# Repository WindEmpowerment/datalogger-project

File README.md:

[Development branch!]

This work is HIGHTLY inspired by the openenergymonitor project.

All the work on this repo is under GNU GPL3 licence.

# datalogger-project (EN)
Datalogger's development in order to monitor a wind turbine (wind speed, wind direction, power).

This work is an initiative by Gilles LONGUET from Tripalium and the Measurment working group from WindEmpowerment.

# Organisation :
This datalogger is design on two principal boards, one for the sensor signal adaptation on a second for the numerical work.
Plug the first on the second and you have the hardware to monitor a wind turbine with these possibilities :
- 2 anemometers
- 1 windvane
- 1 AC voltage sensor
- 1 DC voltage sensor
- 4 DC/AC current sensors
- 1 RPM sensors
- 1 temperature sensor
	
The data is available on an UART permanently and with the UART to USB converter you can collect them directly on a computer.
Data can be write on the SD card too.
To transmit the data, you need to chose a transmitter. You can connect a ESP wifi module to send it on your local network or use a GPRS module to transmit on a remote network.
Emoncms is used to collect data on a remote server, to add process on and record data. It's also used to visualize data.

# datalogger-project (FR)
Développement d'un enregistreur de données pour monitorer une éolienne (vitesse et direction du vent et puissance produite).

Ce travail est une initiative de Gilles Longuet pour Tripalium et le Measurment working group de WindEmpowerment.

# Organisation :
Cet enregistreur de données est développé autour de deux cartes, une première pour le traitement des signaux provenant des capteurs et une seconde pour tout le traitement numérique des données.
Il suffit de connecter la première carte sur la seconde pour avoir un enregistreur de données avec les possibilités suivantes :
- 2 anémomètres
- 1 girouette
- 1 sonde de tension AC
- 1 sonde de tension DC
- 4 sondes de courant AC ou DC
- 1 sonde RPM
- 1 sonde de température
	
Les données sont disponibles sur un UART de façon permanente et avec l'adaptateur UART/USB vous pouvez directement collecter les données sur un ordinateur. Les données peuvent aussi être enregistré sur une carte SD.
Pour transmettre les données, vous devez choisir un module. Soit vous utilisez un module du type ESP wifi, pour envoyer vos données sur votre wifi local. Soit vous utilisez un module GPRS pour transmettre les donnés à distances.
Emoncms est utilisé pour la collecte des données sur un serveur distant. On peut appliquer sur les données des processus puis les enregistrer. Emoncms permet aussi la visualisation des données.

# Repositories description :
## Emoncms_add-ons repo :
Contain different add-ons to simplify the wind visualization.

## Firmware :
Contain the software for the microcontroller.

## Hardware :
Contain the files on the different hardware boards.

## windlogger_shield(old) repo :
Contain the work than was done by Etienne, a student. He does that to help us for an internship of 6 weeks. This is an archive, the new version is in the Hardware repo.
The report is in French.

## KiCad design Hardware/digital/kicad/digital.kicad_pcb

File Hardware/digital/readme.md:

# DIGITALs
This board contains all the needs to use an Atmega1284p like an Arduino. But because it's a prototype board, the power is a small shield to be upgradable. On this digital board, the shield can be plug.
A sd card module and a transmitter module can be add too. This permit to collect data on the SD card and/or send it by wifi or gprs.

## BLOCK DIAGRAM

todo

## RENDER PREVIEW

## Todo list
- test
- documentation...

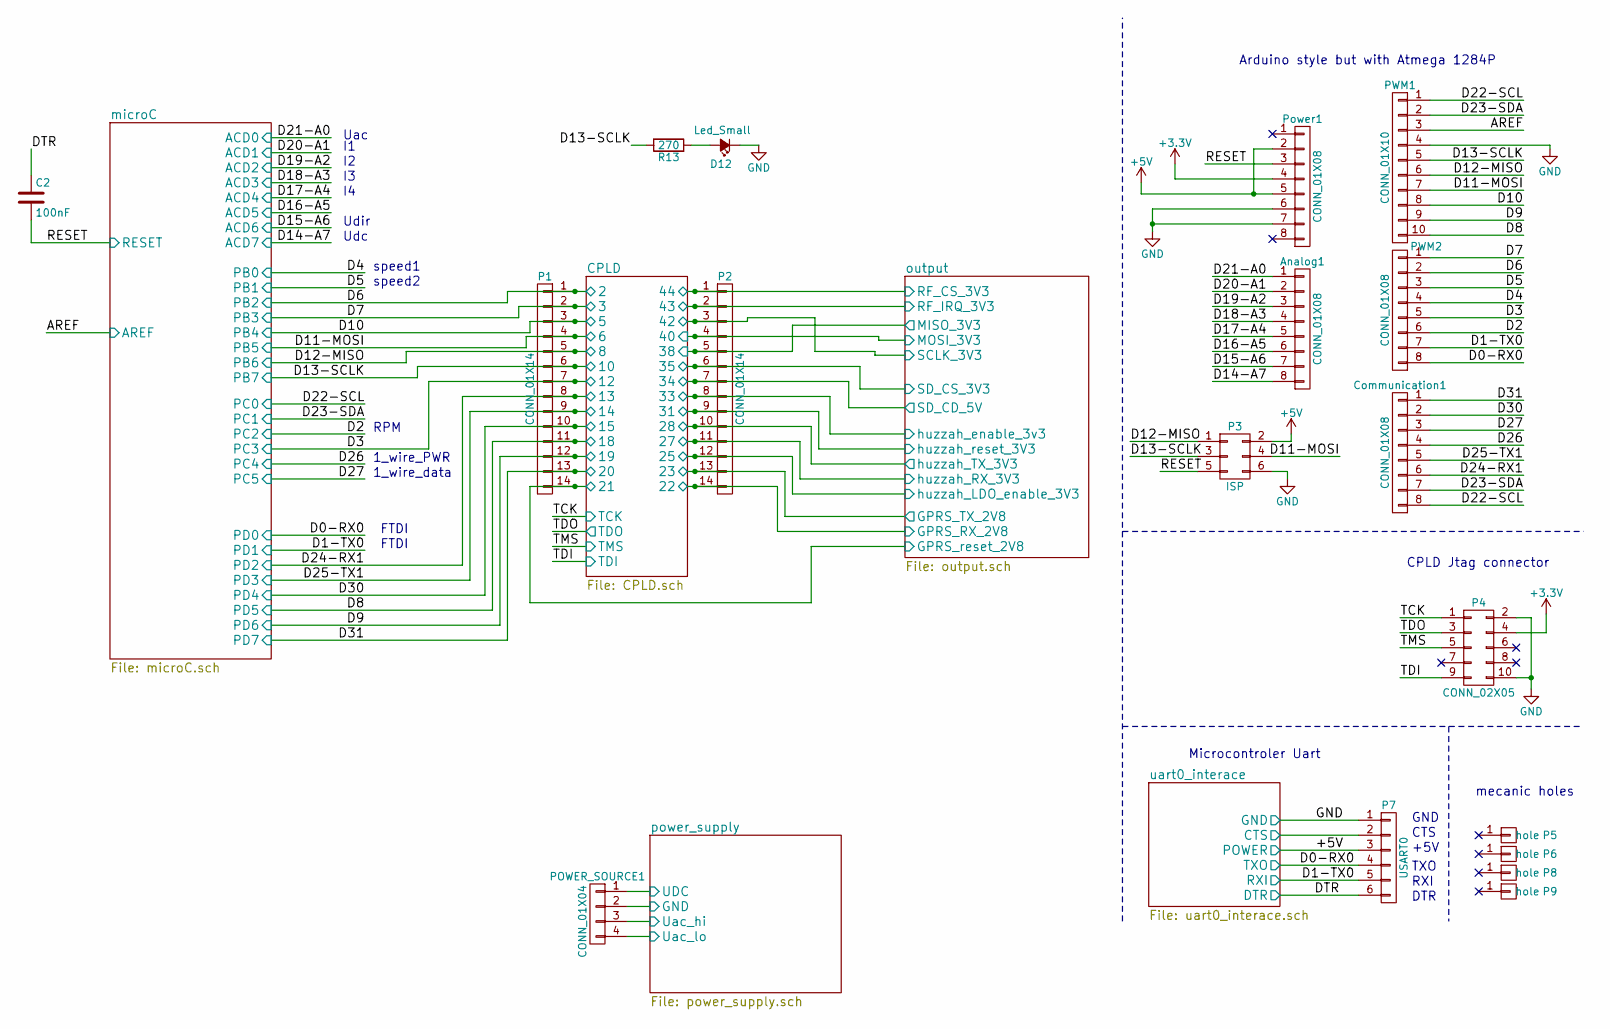
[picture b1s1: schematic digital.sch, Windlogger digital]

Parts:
Analog1: CONN_01X08; Socket_Strip_Straight_1x08
C2: 100nF; C_Rect_L7_W2.5_P5
Communication1: CONN_01X08; Socket_Strip_Straight_1x08
D12: Led_Small; LED-3MM
P1, P2: CONN_01X14; Socket_Strip_Straight_1x14
P3: ISP; Socket_Strip_Straight_2x03
P4: CONN_02X05; Pin_Header_Straight_2x05
P5, P6, P8, P9: hole; Arduino_1pin
P7: USART0; Pin_Header_Straight_1x06
POWER_SOURCE1: CONN_01X04; Socket_Strip_Straight_1x04
PWM1: CONN_01X10; Socket_Strip_Straight_1x10
PWM2: CONN_01X08; Socket_Strip_Straight_1x08
Power1: CONN_01X08; Socket_Strip_Straight_1x08
R13: 270; R3-LARGE_PADS

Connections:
+3V3: P4.4, Power1.4; also elsewhere on the board
+5V: P3.2, P7.3, Power1.2, Power1.5; also elsewhere on the board
/CPLD/2: P1.1, PWM2.2; also elsewhere on the board
/CPLD/3: P1.2, PWM2.1; also elsewhere on the board
/CPLD/5: P1.3, PWM1.8; also elsewhere on the board
/CPLD/6: P1.4, P3.4, PWM1.7; also elsewhere on the board
/CPLD/8: P1.5, P3.1, PWM1.6; also elsewhere on the board
/CPLD/10: P1.6, P3.3, PWM1.5, R13.2; also elsewhere on the board
/CPLD/12: P1.7, PWM2.5; also elsewhere on the board
/CPLD/13: Communication1.6, P1.8; also elsewhere on the board
/CPLD/14: Communication1.5, P1.9; also elsewhere on the board
/CPLD/15: Communication1.2, P1.10; also elsewhere on the board
/CPLD/18: P1.11, PWM1.10; also elsewhere on the board
/CPLD/19: P1.12, PWM1.9; also elsewhere on the board
/CPLD/20: Communication1.1, P1.13; also elsewhere on the board
/CPLD/21: P1.14; also elsewhere on the board
/CPLD/22: P2.14; also elsewhere on the board
/CPLD/23: P2.13; also elsewhere on the board
/CPLD/25: P2.12; also elsewhere on the board
/CPLD/27: P2.11; also elsewhere on the board
/CPLD/28: P2.10; also elsewhere on the board
/CPLD/31: P2.9; also elsewhere on the board
/CPLD/33: P2.8; also elsewhere on the board
/CPLD/34: P2.7; also elsewhere on the board
/CPLD/35: P2.6; also elsewhere on the board
/CPLD/38: P2.5; also elsewhere on the board
/CPLD/40: P2.4; also elsewhere on the board
/CPLD/42: P2.3; also elsewhere on the board
/CPLD/43: P2.2; also elsewhere on the board
/CPLD/44: P2.1; also elsewhere on the board
/CPLD/TCK: P4.1; also elsewhere on the board
/CPLD/TDI: P4.9; also elsewhere on the board
/CPLD/TDO: P4.3; also elsewhere on the board
/CPLD/TMS: P4.5; also elsewhere on the board
/microC/ACD0: Analog1.1; also elsewhere on the board
/microC/ACD1: Analog1.2; also elsewhere on the board
/microC/ACD2: Analog1.3; also elsewhere on the board
/microC/ACD3: Analog1.4; also elsewhere on the board
/microC/ACD4: Analog1.5; also elsewhere on the board
/microC/ACD5: Analog1.6; also elsewhere on the board
/microC/ACD6: Analog1.7; also elsewhere on the board
/microC/ACD7: Analog1.8; also elsewhere on the board
/microC/AREF: PWM1.3; also elsewhere on the board
/microC/PB0: PWM2.4; also elsewhere on the board
/microC/PB1: PWM2.3; also elsewhere on the board
/microC/PC0: Communication1.8, PWM1.1; also elsewhere on the board
/microC/PC1: Communication1.7, PWM1.2; also elsewhere on the board
/microC/PC2: PWM2.6; also elsewhere on the board
/microC/PC4: Communication1.4; also elsewhere on the board
/microC/PC5: Communication1.3; also elsewhere on the board
/microC/PD0: P7.4, PWM2.8; also elsewhere on the board
/microC/PD1: P7.5, PWM2.7; also elsewhere on the board
/microC/RESET: C2.2, P3.5, Power1.3; also elsewhere on the board
/power_supply/UDC: POWER_SOURCE1.1; also elsewhere on the board
/power_supply/Uac_hi: POWER_SOURCE1.3; also elsewhere on the board
/power_supply/Uac_lo: POWER_SOURCE1.4; also elsewhere on the board
/uart0_interace/CTS: P7.2; also elsewhere on the board
/uart0_interace/DTR: C2.1, P7.6; also elsewhere on the board
GND: D12.1 (K), P3.6, P4.2, P4.10, P7.1, POWER_SOURCE1.2, PWM1.4, Power1.6, Power1.7; also elsewhere on the board
unnamed: D12.2 (A), R13.1

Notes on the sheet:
mecanic holes
Arduino style but with Atmega 1284P
DTR
RXI
TXO
GND
+5V
CTS
CPLD Jtag connector
Microcontroler Uart
Uac
Udir
Udc
speed1
speed2
1_wire_PWR
1_wire_data
FTDI
RPM

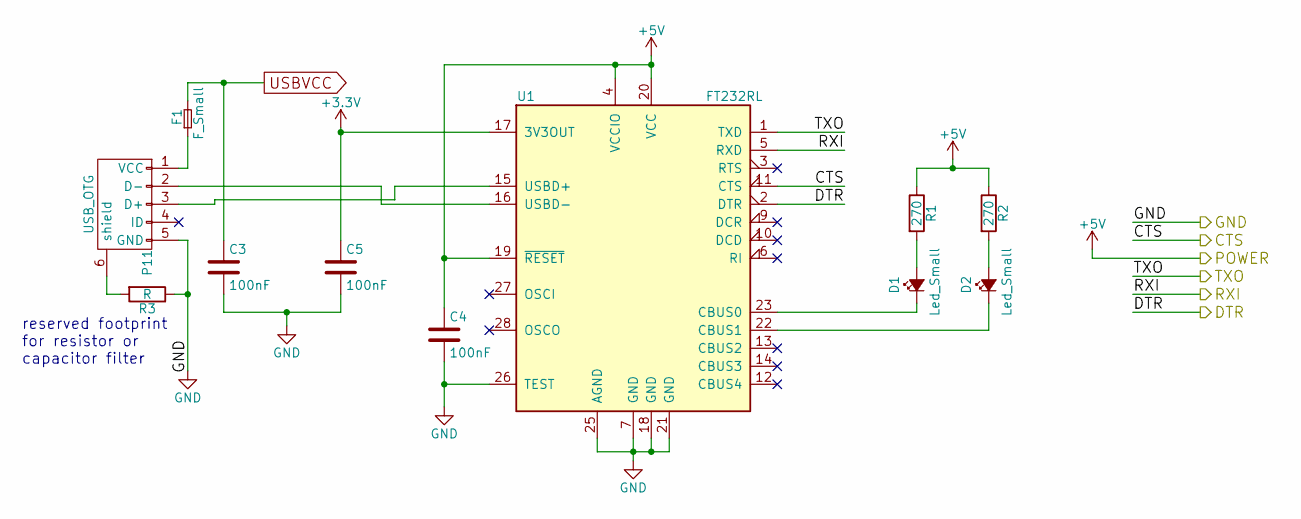
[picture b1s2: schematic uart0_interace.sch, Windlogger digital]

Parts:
C3, C4, C5: 100nF; C_Rect_L7_W2.5_P5
D1, D2: Led_Small; LED-3MM
F1: F_Small; Fuse_TE5_Littlefuse-395Series
P11: USB_OTG; USB_Micro-B_10103594-0001LF
R1, R2: 270; R3-LARGE_PADS
R3: R; R3-LARGE_PADS
U1: FT232RL; SSOP-28_5.3x10.2mm_Pitch0.65mm

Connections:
+3V3: C5.1, U1.17 (3V3OUT); also elsewhere on the board
+5V: C4.1, R1.1, R2.1, U1.4 (VCCIO), U1.19 (~RESET~), U1.20 (VCC); also elsewhere on the board
/microC/PD0: U1.1 (TXD); also elsewhere on the board
/microC/PD1: U1.5 (RXD); also elsewhere on the board
/uart0_interace/CTS: U1.11 (CTS); also elsewhere on the board
/uart0_interace/DTR: U1.2 (DTR); also elsewhere on the board
GND: C3.2, C4.2, C5.2, P11.5 (GND), R3.1, U1.7 (GND), U1.18 (GND), U1.21 (GND), U1.25 (AGND), U1.26 (TEST); also elsewhere on the board
unnamed: D1.1 (K), U1.23 (CBUS0)
unnamed: D1.2 (A), R1.2
unnamed: D2.1 (K), U1.22 (CBUS1)
unnamed: D2.2 (A), R2.2
unnamed: F1.1, P11.1 (VCC)
unnamed: P11.2 (D-), U1.16 (USBD-)
unnamed: P11.3 (D+), U1.15 (USBD+)
unnamed: P11.6 (shield), R3.2
USBVCC: C3.1, F1.2; also elsewhere on the board

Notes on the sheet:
reserved footprint for resistor or capacitor filter

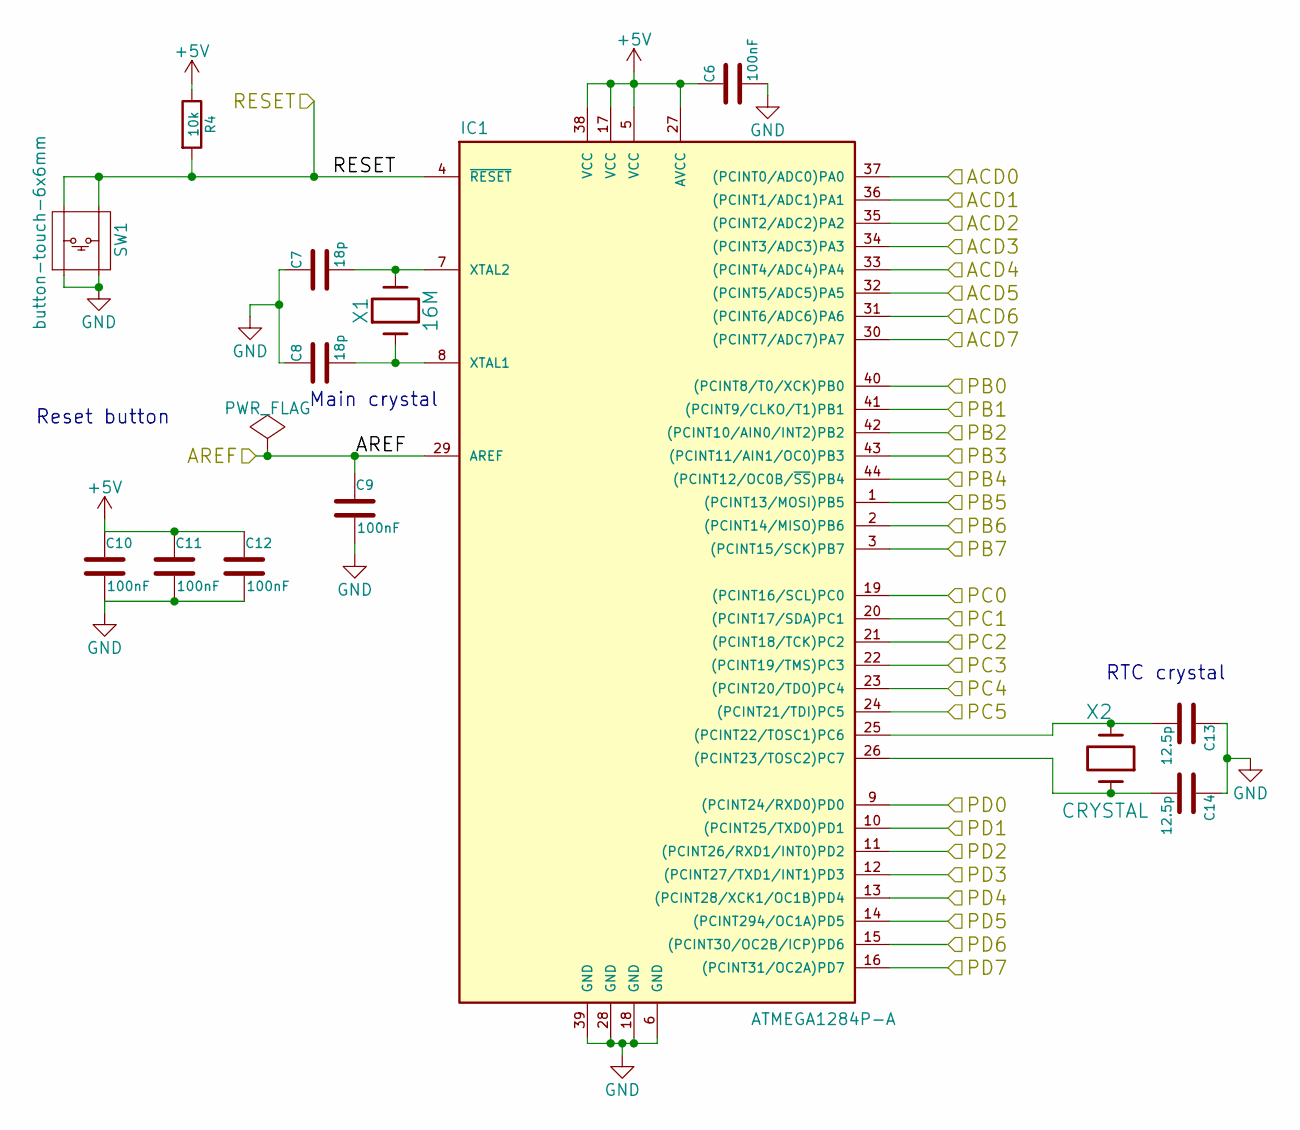
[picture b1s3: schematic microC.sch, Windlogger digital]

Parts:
C6, C9, C10, C11, C12: 100nF; C_Rect_L7_W2.5_P5
C7, C8: 18p; C_Rect_L4_W2.5_P2.5
C13, C14: 12.5p; C_Rect_L4_W2.5_P2.5
IC1: ATMEGA1284P-A; TQFP-44_10x10mm_Pitch0.8mm
R4: 10k; R3-LARGE_PADS
SW1: button-touch-6x6mm
X1: 16M; Crystal_HC49-U_Vertical
X2: CRYSTAL; Crystal_Round_Horizontal_3mm_BigPad

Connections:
+5V: C6.1, C10.1, C11.1, C12.1, IC1.5 (VCC), IC1.17 (VCC), IC1.27 (AVCC), IC1.38 (VCC), R4.1; also elsewhere on the board
/CPLD/2: IC1.42 ((PCINT10/AIN0/INT2)PB2); also elsewhere on the board
/CPLD/3: IC1.43 ((PCINT11/AIN1/OC0)PB3); also elsewhere on the board
/CPLD/5: IC1.44 ((PCINT12/OC0B/~SS~)PB4); also elsewhere on the board
/CPLD/6: IC1.1 ((PCINT13/MOSI)PB5); also elsewhere on the board
/CPLD/8: IC1.2 ((PCINT14/MISO)PB6); also elsewhere on the board
/CPLD/10: IC1.3 ((PCINT15/SCK)PB7); also elsewhere on the board
/CPLD/12: IC1.22 ((PCINT19/TMS)PC3); also elsewhere on the board
/CPLD/13: IC1.11 ((PCINT26/RXD1/INT0)PD2); also elsewhere on the board
/CPLD/14: IC1.12 ((PCINT27/TXD1/INT1)PD3); also elsewhere on the board
/CPLD/15: IC1.13 ((PCINT28/XCK1/OC1B)PD4); also elsewhere on the board
/CPLD/18: IC1.14 ((PCINT294/OC1A)PD5); also elsewhere on the board
/CPLD/19: IC1.15 ((PCINT30/OC2B/ICP)PD6); also elsewhere on the board
/CPLD/20: IC1.16 ((PCINT31/OC2A)PD7); also elsewhere on the board
/microC/ACD0: IC1.37 ((PCINT0/ADC0)PA0); also elsewhere on the board
/microC/ACD1: IC1.36 ((PCINT1/ADC1)PA1); also elsewhere on the board
/microC/ACD2: IC1.35 ((PCINT2/ADC2)PA2); also elsewhere on the board
/microC/ACD3: IC1.34 ((PCINT3/ADC3)PA3); also elsewhere on the board
/microC/ACD4: IC1.33 ((PCINT4/ADC4)PA4); also elsewhere on the board
/microC/ACD5: IC1.32 ((PCINT5/ADC5)PA5); also elsewhere on the board
/microC/ACD6: IC1.31 ((PCINT6/ADC6)PA6); also elsewhere on the board
/microC/ACD7: IC1.30 ((PCINT7/ADC7)PA7); also elsewhere on the board
/microC/AREF: C9.1, IC1.29 (AREF); also elsewhere on the board
/microC/PB0: IC1.40 ((PCINT8/T0/XCK)PB0); also elsewhere on the board
/microC/PB1: IC1.41 ((PCINT9/CLKO/T1)PB1); also elsewhere on the board
/microC/PC0: IC1.19 ((PCINT16/SCL)PC0); also elsewhere on the board
/microC/PC1: IC1.20 ((PCINT17/SDA)PC1); also elsewhere on the board
/microC/PC2: IC1.21 ((PCINT18/TCK)PC2); also elsewhere on the board
/microC/PC4: IC1.23 ((PCINT20/TDO)PC4); also elsewhere on the board
/microC/PC5: IC1.24 ((PCINT21/TDI)PC5); also elsewhere on the board
/microC/PD0: IC1.9 ((PCINT24/RXD0)PD0); also elsewhere on the board
/microC/PD1: IC1.10 ((PCINT25/TXD0)PD1); also elsewhere on the board
/microC/RESET: IC1.4 (~RESET), R4.2, SW1.2, SW1.4; also elsewhere on the board
GND: C6.2, C7.1, C8.1, C9.2, C10.2, C11.2, C12.2, C13.1, C14.1, IC1.6 (GND), IC1.18 (GND), IC1.28 (GND), IC1.39 (GND), SW1.1, SW1.3; also elsewhere on the board
unnamed: C7.2, IC1.7 (XTAL2), X1.2
unnamed: C8.2, IC1.8 (XTAL1), X1.1
unnamed: C13.2, IC1.25 ((PCINT22/TOSC1)PC6), X2.2
unnamed: C14.2, IC1.26 ((PCINT23/TOSC2)PC7), X2.1

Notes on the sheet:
Main crystal
RTC crystal
Reset button

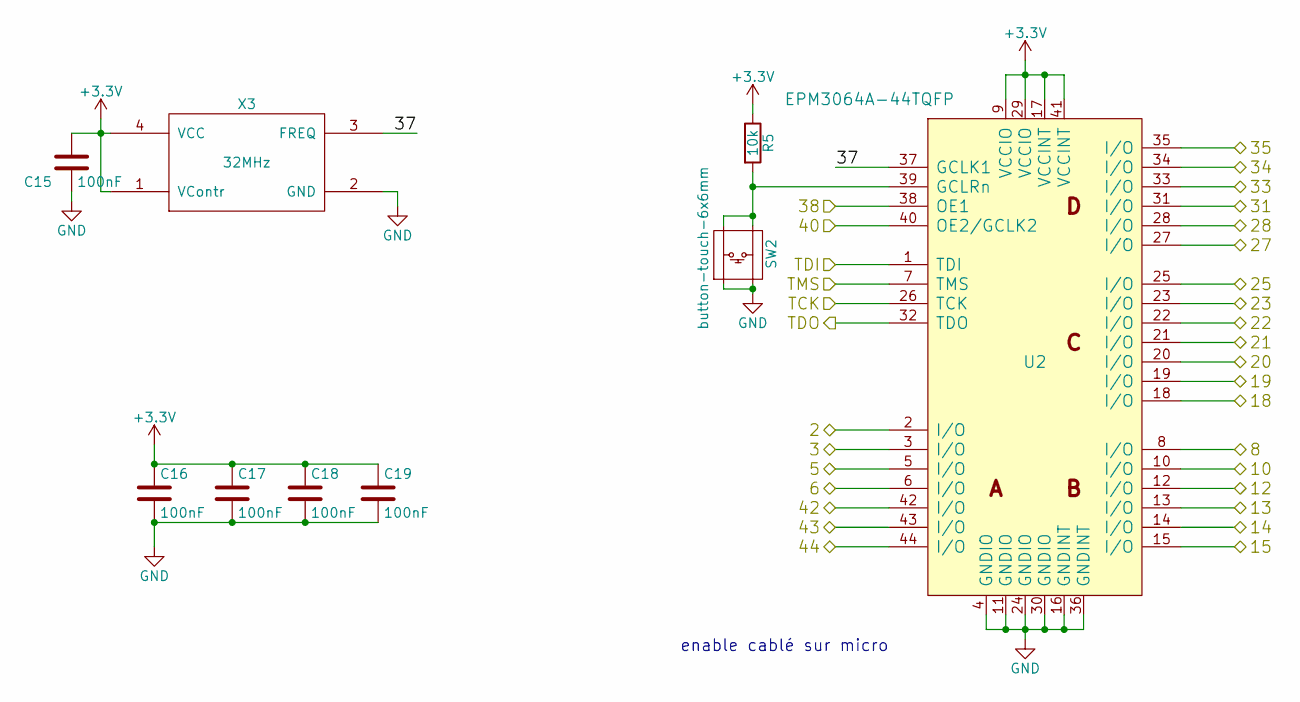
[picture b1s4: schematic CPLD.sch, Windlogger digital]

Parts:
C15, C16, C17, C18, C19: 100nF; C_Rect_L7_W2.5_P5
R5: 10k; R3-LARGE_PADS
SW2: button-touch-6x6mm
U2: EPM3064A-44TQFP; TQFP-44_10x10mm_Pitch0.8mm
X3: 32MHz; oscillator-7x5mm

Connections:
+3V3: C15.1, C16.1, C17.1, C18.1, C19.1, R5.1, U2.9 (VCCIO), U2.17 (VCCINT), U2.29 (VCCIO), U2.41 (VCCINT), X3.1 (VContr), X3.4 (VCC); also elsewhere on the board
/CPLD/2: U2.2 (I/O); also elsewhere on the board
/CPLD/3: U2.3 (I/O); also elsewhere on the board
/CPLD/5: U2.5 (I/O); also elsewhere on the board
/CPLD/6: U2.6 (I/O); also elsewhere on the board
/CPLD/8: U2.8 (I/O); also elsewhere on the board
/CPLD/10: U2.10 (I/O); also elsewhere on the board
/CPLD/12: U2.12 (I/O); also elsewhere on the board
/CPLD/13: U2.13 (I/O); also elsewhere on the board
/CPLD/14: U2.14 (I/O); also elsewhere on the board
/CPLD/15: U2.15 (I/O); also elsewhere on the board
/CPLD/18: U2.18 (I/O); also elsewhere on the board
/CPLD/19: U2.19 (I/O); also elsewhere on the board
/CPLD/20: U2.20 (I/O); also elsewhere on the board
/CPLD/21: U2.21 (I/O); also elsewhere on the board
/CPLD/22: U2.22 (I/O); also elsewhere on the board
/CPLD/23: U2.23 (I/O); also elsewhere on the board
/CPLD/25: U2.25 (I/O); also elsewhere on the board
/CPLD/27: U2.27 (I/O); also elsewhere on the board
/CPLD/28: U2.28 (I/O); also elsewhere on the board
/CPLD/31: U2.31 (I/O); also elsewhere on the board
/CPLD/33: U2.33 (I/O); also elsewhere on the board
/CPLD/34: U2.34 (I/O); also elsewhere on the board
/CPLD/35: U2.35 (I/O); also elsewhere on the board
/CPLD/37: U2.37 (GCLK1), X3.3 (FREQ)
/CPLD/38: U2.38 (OE1); also elsewhere on the board
/CPLD/40: U2.40 (OE2/GCLK2); also elsewhere on the board
/CPLD/42: U2.42 (I/O); also elsewhere on the board
/CPLD/43: U2.43 (I/O); also elsewhere on the board
/CPLD/44: U2.44 (I/O); also elsewhere on the board
/CPLD/TCK: U2.26 (TCK); also elsewhere on the board
/CPLD/TDI: U2.1 (TDI); also elsewhere on the board
/CPLD/TDO: U2.32 (TDO); also elsewhere on the board
/CPLD/TMS: U2.7 (TMS); also elsewhere on the board
GND: C15.2, C16.2, C17.2, C18.2, C19.2, SW2.1, SW2.3, U2.4 (GNDIO), U2.11 (GNDIO), U2.16 (GNDINT), U2.24 (GNDIO), U2.30 (GNDIO), U2.36 (GNDINT), X3.2 (GND); also elsewhere on the board
unnamed: R5.2, SW2.2, SW2.4, U2.39 (GCLRn)

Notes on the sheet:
enable cablé sur micro

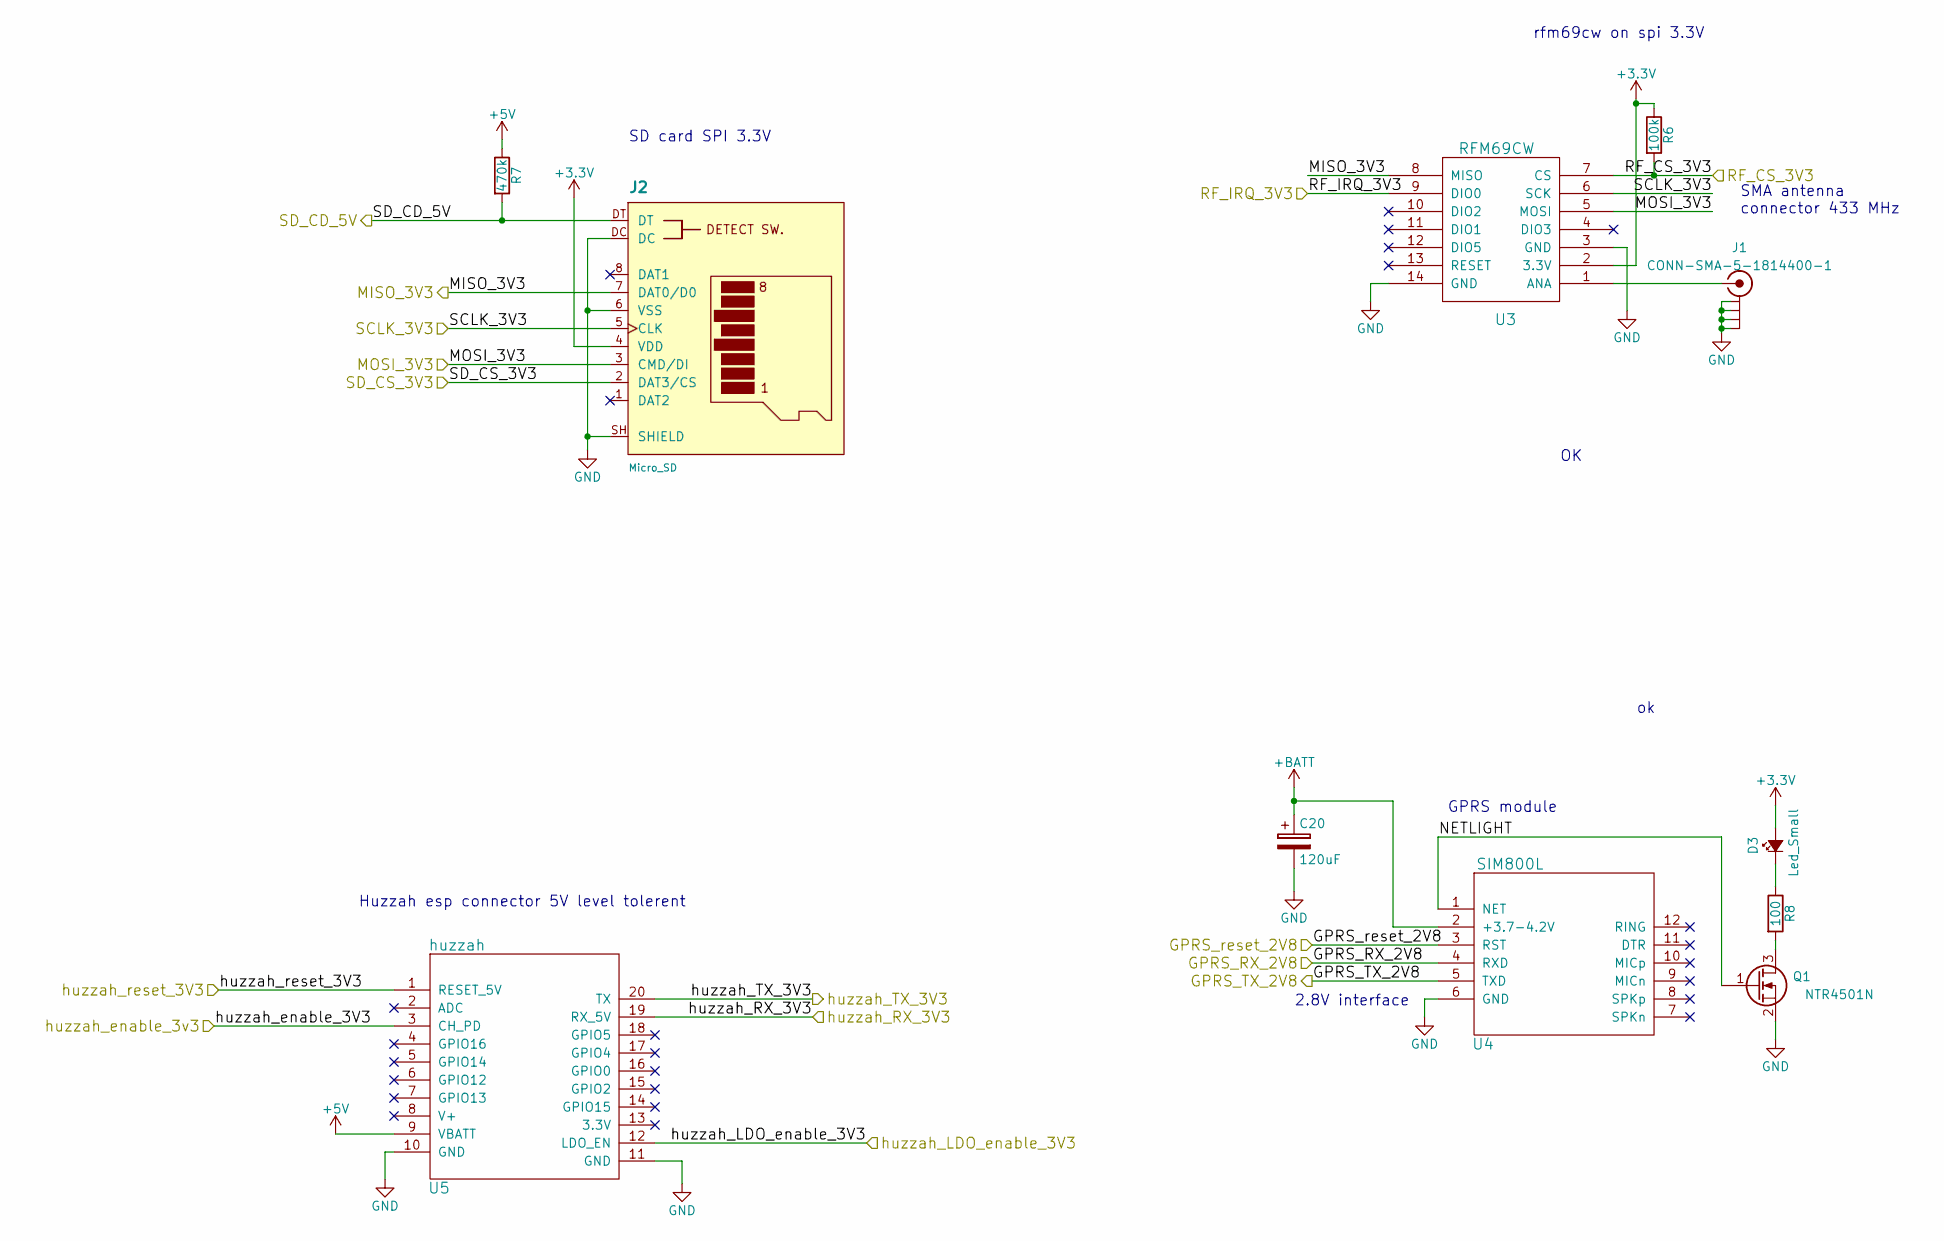
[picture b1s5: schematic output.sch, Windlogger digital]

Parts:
C20: 120uF; C_Radial_D6.3_L11.2_P2.5
D3: Led_Small; LED-3MM
J1: CONN-SMA-5-1814400-1; conn-SMA_TE-5-1814400-1
J2: Micro_SD; HIROSE-MICROSD-DM3AT-SF
Q1: NTR4501N; SOT-23_Handsoldering
R6: 100k; R3-LARGE_PADS
R7: 470k; R3-LARGE_PADS
R8: 100; R3-LARGE_PADS
U3: RFM69CW
U4: SIM800L; GPRS-SIM80L-smaller
U5: huzzah; adafruit-huzzah

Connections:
+3V3: D3.2 (A), J2.4 (VDD), R6.1, U3.2 (3.3V); also elsewhere on the board
+5V: R7.1, U5.9 (VBATT); also elsewhere on the board
+BATT: C20.1, U4.2 (+3.7-4.2V); also elsewhere on the board
/CPLD/21: U4.3 (RST); also elsewhere on the board
/CPLD/22: U4.4 (RXD); also elsewhere on the board
/CPLD/23: U4.5 (TXD); also elsewhere on the board
/CPLD/25: U5.12 (LDO_EN); also elsewhere on the board
/CPLD/27: U5.19 (RX_5V); also elsewhere on the board
/CPLD/28: U5.20 (TX); also elsewhere on the board
/CPLD/31: U5.1 (RESET_5V); also elsewhere on the board
/CPLD/33: U5.3 (CH_PD); also elsewhere on the board
/CPLD/34: J2.DT, R7.2; also elsewhere on the board
/CPLD/35: J2.2 (DAT3/CS); also elsewhere on the board
/CPLD/38: J2.7 (DAT0/D0), U3.8 (MISO); also elsewhere on the board
/CPLD/40: J2.3 (CMD/DI), U3.5 (MOSI); also elsewhere on the board
/CPLD/42: J2.5 (CLK), U3.6 (SCK); also elsewhere on the board
/CPLD/43: U3.9 (DIO0); also elsewhere on the board
/CPLD/44: R6.2, U3.7 (CS); also elsewhere on the board
/output/NETLIGHT: Q1.1 (G), U4.1 (NET)
GND: C20.2, J1.2, J1.3, J1.4, J1.5, J2.6 (VSS), J2.DC, J2.SH (SHIELD), Q1.2 (S), U3.3 (GND), U3.14 (GND), U4.6 (GND), U5.10 (GND), U5.11 (GND); also elsewhere on the board
unnamed: D3.1 (K), R8.1
unnamed: J1.1, U3.1 (ANA)
unnamed: Q1.3 (D), R8.2

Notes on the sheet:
rfm69cw on spi 3.3V
Huzzah esp connector 5V level tolerent
GPRS module
SD card SPI 3.3V
2.8V interface
SMA antenna connector 433 MHz

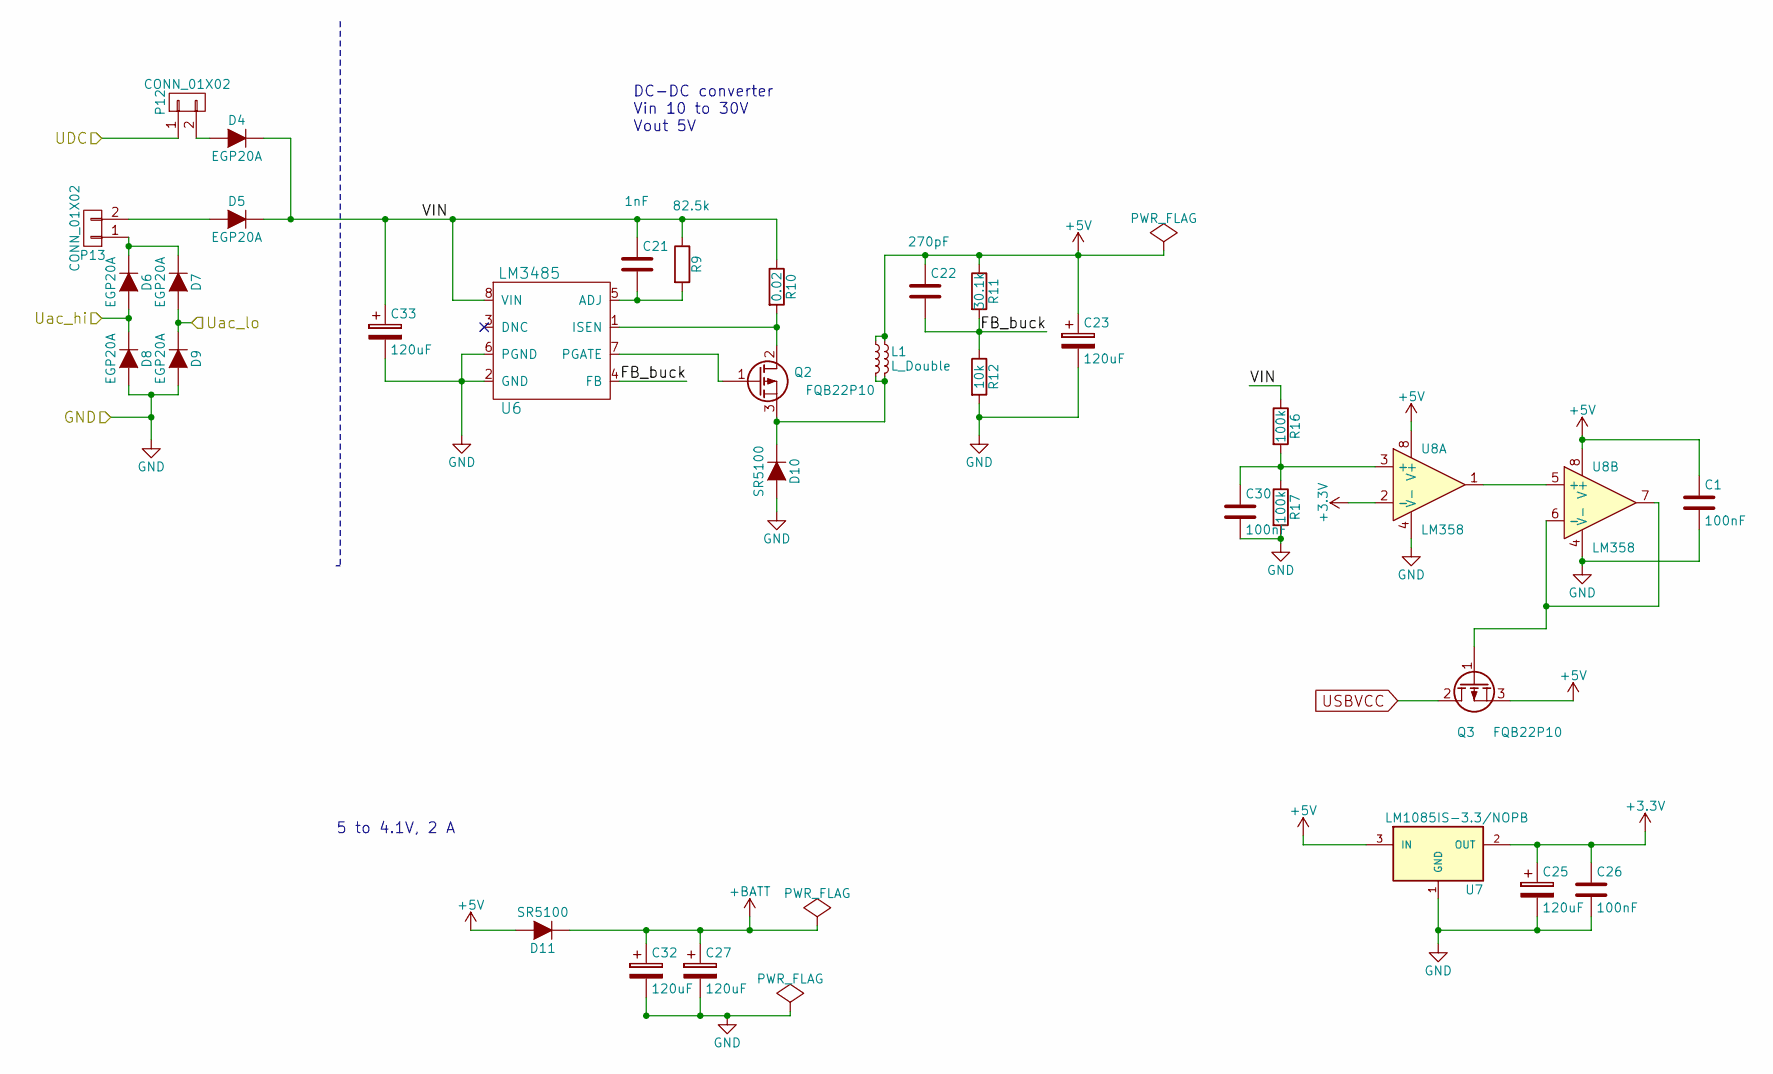
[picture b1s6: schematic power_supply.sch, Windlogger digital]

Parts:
C1, C26, C30: 100nF; C_Rect_L7_W2.5_P5
C21: 1nF; C_Rect_L7_W2.5_P5
C22: 270pF; C_Rect_L4_W2.5_P2.5
C23, C25, C27, C32, C33: 120uF; C_Radial_D6.3_L11.2_P2.5
D4, D5, D6, D7, D8, D9: EGP20A; Diode_DO-35_SOD27_Horizontal_RM10
D10, D11: SR5100; Diode_DO-35_SOD27_Horizontal_RM10
L1: L_Double; DRQ_127
P12, P13: CONN_01X02; Pin_Header_Straight_1x02
Q2, Q3: FQB22P10; D2PAK_2pins
R9: 82.5k; R3-LARGE_PADS
R10: 0.02; R4-LARGE_PADS
R11: 30.1k; R3-LARGE_PADS
R12: 10k; R3-LARGE_PADS
R16, R17: 100k; R3-LARGE_PADS
U6: LM3485; MSOP-8_3x3mm_Pitch0.65mm
U7: LM1085IS-3.3/NOPB; D2PAK_3pins
U8: LM358; DIP-8_W7.62mm_LongPads

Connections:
+3V3: C25.1, C26.1, U7.2 (OUT), U8.2 (-); also elsewhere on the board
+5V: C1.1, C22.1, C23.1, D11.2 (A), L1.1, L1.2, Q3.3 (S), R11.1, U7.3 (IN), U8.8 (V+); also elsewhere on the board
+BATT: C27.1, C32.1, D11.1 (K); also elsewhere on the board
/power_supply/FB_buck: C22.2, R11.2, R12.1, U6.4 (FB)
/power_supply/UDC: P12.1; also elsewhere on the board
/power_supply/Uac_hi: D6.2 (A), D8.1 (K); also elsewhere on the board
/power_supply/Uac_lo: D7.2 (A), D9.1 (K); also elsewhere on the board
/power_supply/VIN: C21.1, C33.1, D4.1 (K), D5.1 (K), R9.1, R10.1, R16.1, U6.8 (VIN)
GND: C1.2, C23.2, C25.2, C26.2, C27.2, C30.2, C32.2, C33.2, D8.2 (A), D9.2 (A), D10.2 (A), R12.2, R17.2, U6.2 (GND), U6.6 (PGND), U7.1 (GND), U8.4 (V-); also elsewhere on the board
unnamed: C21.2, R9.2, U6.5 (ADJ)
unnamed: C30.1, R16.2, R17.1, U8.3 (+)
unnamed: D4.2 (A), P12.2
unnamed: D5.2 (A), P13.2
unnamed: D6.1 (K), D7.1 (K), P13.1
unnamed: D10.1 (K), L1.3, L1.4, Q2.3 (S)
unnamed: Q2.1 (G), U6.7 (PGATE)
unnamed: Q2.2 (D), R10.2, U6.1 (ISEN)
unnamed: Q3.1 (G), U8.6 (-), U8.7
unnamed: U8.1, U8.5 (+)
USBVCC: Q3.2 (D); also elsewhere on the board

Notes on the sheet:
DC-DC converter Vin 10 to 30V Vout 5V
5 to 4.1V, 2 A

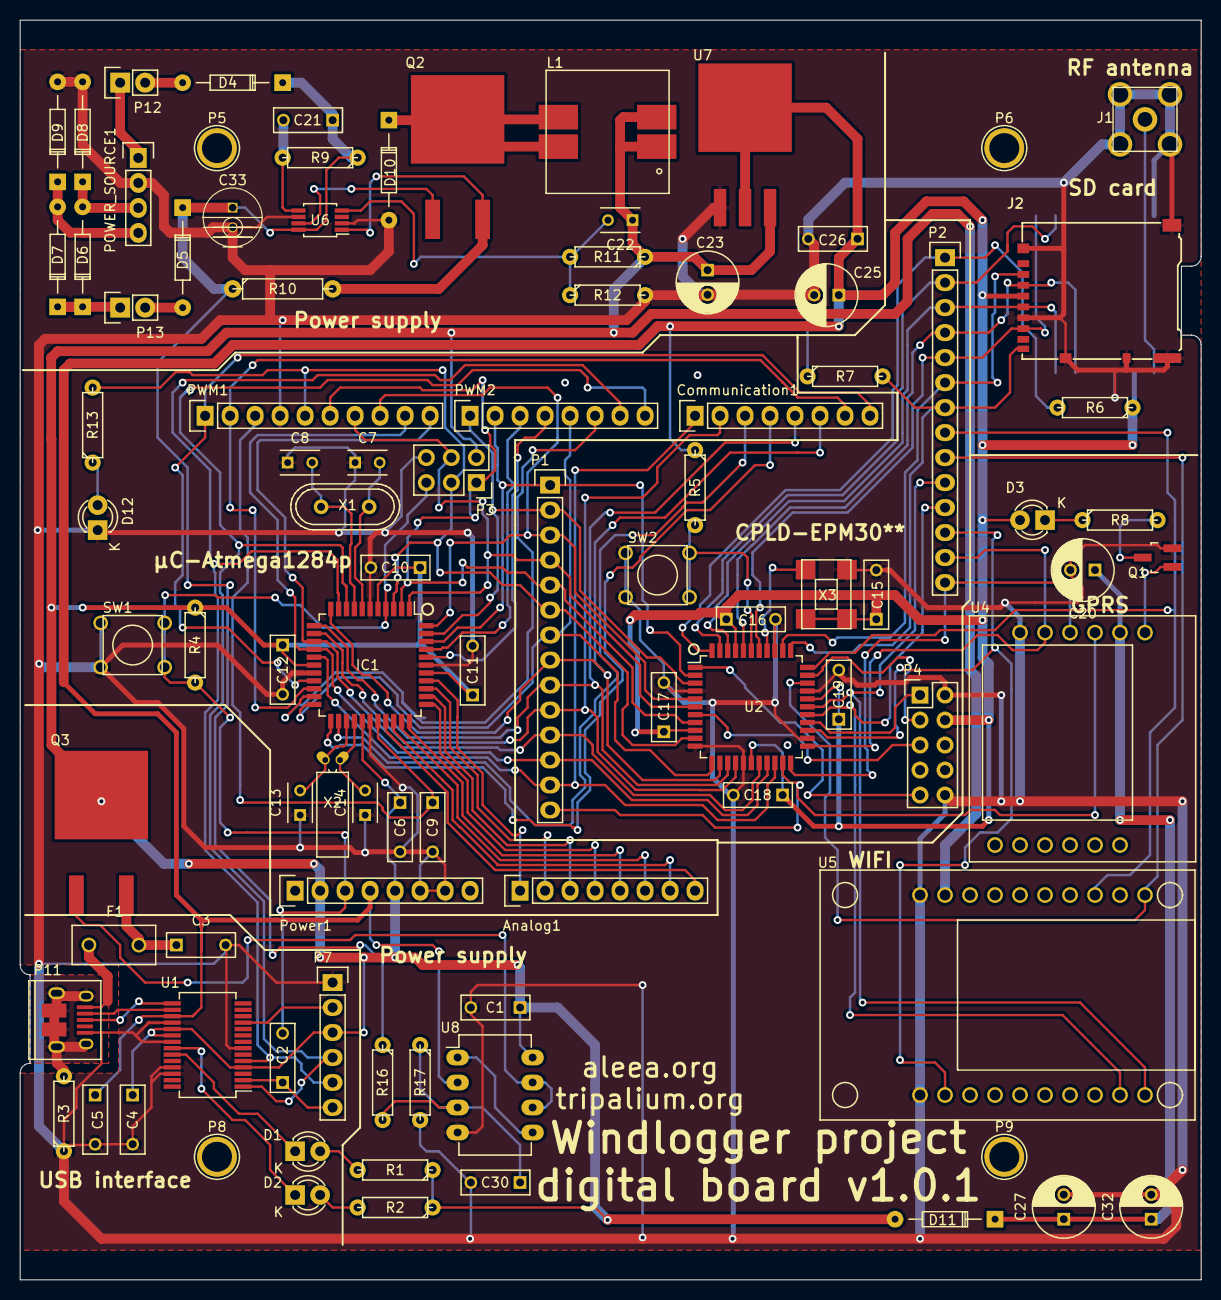
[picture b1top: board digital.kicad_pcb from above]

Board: 2 copper layers, 120.0 x 128.0 mm, 95 parts (1 on the bottom side), 92 nets.

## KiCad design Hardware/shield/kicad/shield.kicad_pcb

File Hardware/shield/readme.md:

# SHIELD
This board contains the functions to convert the signals from sensors to signals for the microcontroller.

This board is design to be plug in the digital board, but you can use it with an arduino uno or mega.

Comment are insert in the schematic, open the kicad project or the pdf export to read those.

## BLOCK DIAGRAM

## RENDER PREVIEW

## Todo list
- chose the componants
- update the BOM
- route the board
- test

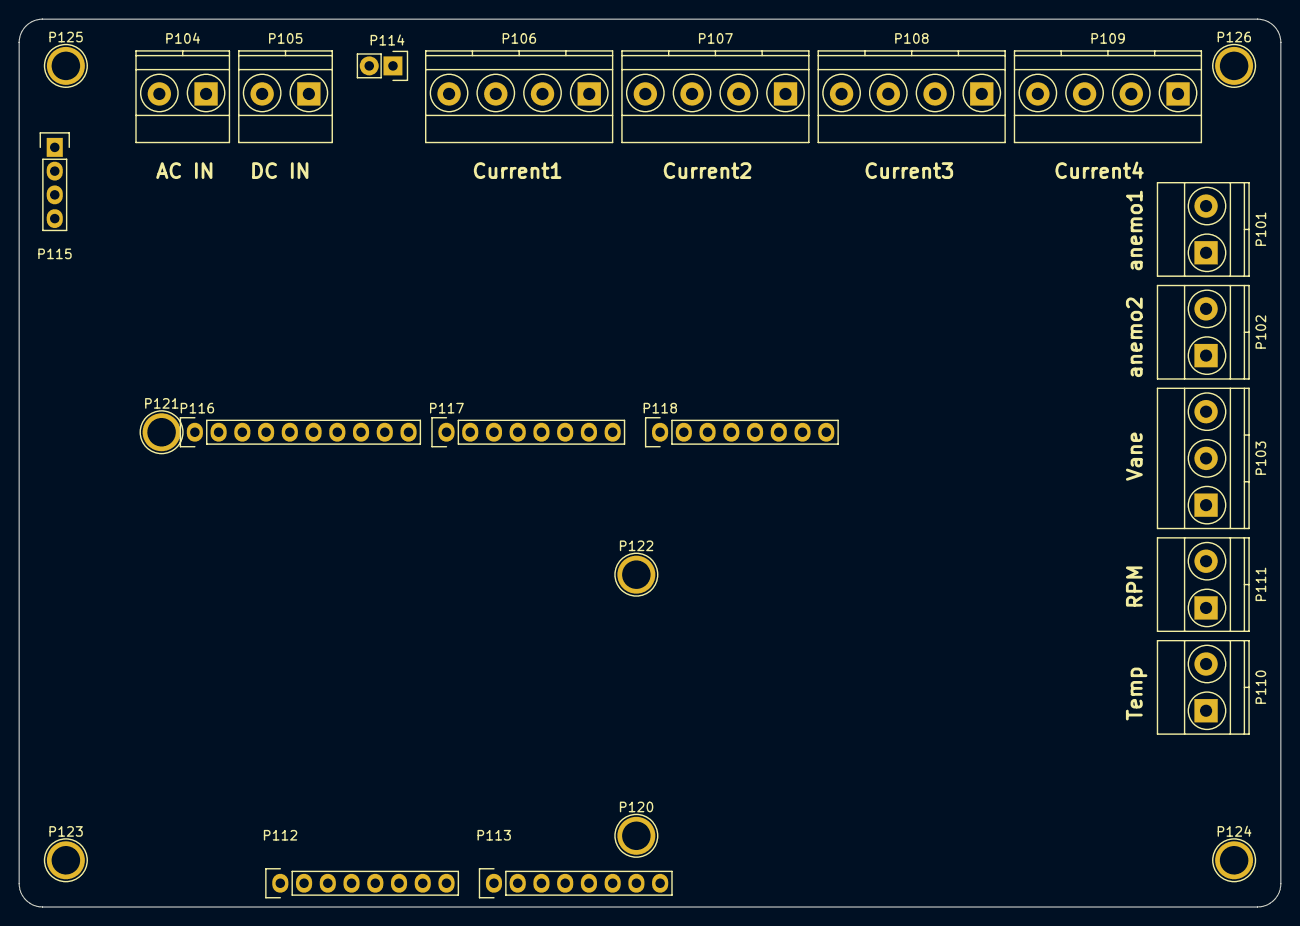
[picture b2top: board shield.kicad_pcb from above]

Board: 2 copper layers, 135.0 x 95.0 mm, 25 parts (0 on the bottom side), 6 nets, no tracks yet.

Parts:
P101: anemo1; TerminalBlock_Pheonix_MKDS1.5-2pol
P102: anemo2; TerminalBlock_Pheonix_MKDS1.5-2pol
P103: vane; TerminalBlock_Pheonix_MKDS1.5-3pol
P104: AC_in; TerminalBlock_Pheonix_MKDS1.5-2pol
P105: DC_in; TerminalBlock_Pheonix_MKDS1.5-2pol
P106: current1; TerminalBlock_Pheonix_MKDS1.5-4pol
P107: current2; TerminalBlock_Pheonix_MKDS1.5-4pol
P108: current3; TerminalBlock_Pheonix_MKDS1.5-4pol
P109: current4; TerminalBlock_Pheonix_MKDS1.5-4pol
P110: temp; TerminalBlock_Pheonix_MKDS1.5-2pol
P111: RPM; TerminalBlock_Pheonix_MKDS1.5-2pol
P112: Power; Socket_Strip_Arduino_1x08
P113: Analog; Socket_Strip_Arduino_1x08
P114: 5VDC; Socket_Strip_Straight_1x02
P115: POWER_SOURCE; Socket_Strip_Straight_1x04
P116: PWM; Socket_Strip_Arduino_1x10
P117: PWM; Socket_Strip_Arduino_1x08
P118: Communication; Socket_Strip_Arduino_1x08
P120: h2; Arduino_1pin
P121: h3; Arduino_1pin
P122: h4; Arduino_1pin
P123: h5; Arduino_1pin
P124: h6; Arduino_1pin
P125: h7; Arduino_1pin
P126: h8; Arduino_1pin

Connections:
+5V: P106.4, P107.4, P108.4, P109.4, P112.5, P114.2
/F3_Voltage_sensors/UAC_hi: P104.2, P115.3
/F3_Voltage_sensors/UAC_lo: P104.1, P115.4
/F3_Voltage_sensors/Ubat: P105.2, P115.1
/RPM: P111.2, P117.1
GND: P101.1, P102.1, P105.1, P106.3, P107.3, P108.3, P109.3, P111.1, P112.6, P112.7, P114.1, P115.2, P116.4

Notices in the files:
Hardware/digital/kicad/CPLD.sch:
AGPL3
